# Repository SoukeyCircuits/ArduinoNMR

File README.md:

August 2026 Update and Explainer:

IMPORTANT DISCLAIMER: The repository here is only the spectrometer for an NMR. You will need to purchase a sufficiently homogeneous magnet and a power amplifier to acquire any kind of measurement. A power amplifier can be purchased from aliexpress for under $100 but your quality and safety will vary significantly. If you are looking for a magnet, there are a few open source options that you can build yourself or commercially available ones.

The magnet used for demonstration can be found here: 
https://www.spincore.com/products/Magnets/
I will do a build of this one: 
https://www.hardware-x.com/article/S2468-0672(25)00029-X/fulltext 
I'm unsure if this is of high quality but would be an interesting build:
https://science.slc.edu/mfrey/project/3dprintnmrmandhalas_update2/

To do list: 
	
  -Upload Accessory PCB files
	
  -Add alternative attenuator and LNA (10 MHz minimum frequency but lower price).
	
  -Upload control code
	
  -Upload Arduino NMR pulse code (being edited for release)
	
  -Upload CAD/CAM designs for the housing and end plates
	
  -Add Arduino Giga Display + display software
	
  -Show preliminary results from working device
	
  -Add non JLC BOM (Mouser, Aliexpress, etc)
	
  -Add raspberry pi multiple instrument control software.

  -Fix phase error discovered at OpenSauce 2026.
  
  -Implement digital filtering techniques.
  
The main sections of the Arduino NMR are the RF synthesis, RF input, and the Tayloe detector. 

RF synthesis begins with the SI5351A-B-GM chip connected to an ABM8G-25.000MHZ-4Y-T3, a  25 MHz crystal oscillator. The 20QFN package for the SI5351 was specifically chosen over the 16QFN as it was having issues with the Etherkit SI5351 library and not indexing the clock outputs correctly. The SI5351A-B-GM is still unable to use CLK6 and CLK7 as they are handled differently from CLK0-CLK5. Although it would be possible to control all 8 outputs, the function is sufficient for the design as is. The primary output clocks CLK0-CLK3 are connected to an ADG904BRUZ in an SP4T configuration. The switch allows for indexing either 0°, 90°, 180°, and 270° phase for a single frequency or 0° and a second phase at two separate frequencies. The lowest frequency for a 0°-90° control is 4.76 MHz due to the lower PLL limit of 600 MHz and the upper divider limit of int-127. For 0°-90°-180°, the lower limit is twice that at 9.52 MHz. Finally, for full 0°-90°-180°-270° control, the lower limit is 14.17 MHz.

The output is then fed into a PE4251MLI-Z SPDT switch. Since both single and dual frequency setups have an available channel containing the 0° at the Larmor frequency, when not transmitting, the channel can be used for Homodyne demodulation. Alternatively, one of the clocks can be set to a secondary offset frequency for Heterodyne demodulation. 

When actively transmitting, the output is sent through a PE43650 attenuator for digital control of the RF power output. Although the PE43650 was chosen based on availability and price, it would be advantageous to include the PE43711B-Z as an option in the future. The PE43650 has 0.5 dB step sizes with a maximum attenuation of 15.5 dB, but an improvement with the PE43711B-Z would give 0.25 dB step sizes and a maximum attenuation of 31.5 dB. For these applications, 0.5 dB is sufficient and maximum power can be limited by an external attenuator on the output(s).

fter attenuation, the final stage is either a bridged solder jumper, or another PE4251MLI-Z SPDT switch. This switch is what controls the two TX output options. Each output will need its own external attenuator to limit the maximum power output as well as a filter. The SI5351 only emits a square shaped output and harmonic frequencies must be filtered out for a pure sinusoidal output at the desired frequency. This allows for connecting a single spectrometer to multiple instruments each with their own dedicated TX and RX ports.

After amplification, further accessory parts are available for filtering, conditioning, and pulse breakthrough limitation. All of these accessories fit inside a 50x25x25mm aluminum enclosure available on Aliexpress but require drilling holes for the SMA connectors. The first accessory is the LC filter. This design is able to fit a 7 pole LC filter within the small enclosure for high off frequency rejection for both ≤100W and ≤5W depending on which side is populated. 

Another accompanying accessory is the crossed-diode duplexer to reject low power noise from the amplifier while passing the high powered pulse. By populating the diodes at the top of the design and not populating the lower diodes, this gives a path of 3 pairs of crossed diodes before reaching the center SMA port leading to the magnet. By changing the diodes populated to the bottom half of the board, bridging the top solder jumper, and not including the center SMA header, the same board can be used for crossed diodes to ground. It should be said, never try to combine these two functions as they are for separate uses and it could damage your equipment.

When attempting to capture the NMR signal, always filter before the signal enters the RX ports. Like with the TX ports, the signal can either go into the default solder bridged SMA connector, or be actively switched between the two RX ports. Once the signal has entered the RX portion of the board, there is one additional PE4251MLI-Z SPDT switch to protect the preamplifier from the pulse breakthrough. This switch is normally closed to a 50 Ω terminator but can be GPIO controlled to open after the desired deadtime. When open, the signal passes into a multiple stage low noise amplifier (LNA). The LNA is a dual stage PHA-13HLN+ amplifier with approximately 48-51 dB of gain with a noise figure ≤3. An additional design with budget conscience in mind alternatively uses a dual GALI-S66+ design for $10 instead of $30. This design has a smaller 42 dB gain and has a similar noise figure above 10 MHz but the noise figure skyrockets below 10 MHz. 

After the preamplifier, the design has one of two options for configuration, bridging the triple solder pad to the left, sends the signal directly into the Tayloe detector. Alternatively, bridging the solder to the right and additionally at the end allows for additional filtering after the LNA. If RX1 and RX2 are close in frequency, the filter can be set to cut off just at the frequency of interest. If the desire is for wide band operation from 1-100 MHz, it is advised to still filter the 100+ MHz frequency as both LNAs have additional noise at or above that frequency. The performance of the LNA and accompanying filtering can be measured by disconnecting C43, not powering the 5V line, and connecting to the center SMA connector as the output. It is advised to validate the gain and noise figure of the LNA prior to connecting to the SN74LV4052ADR. 

Once the signal is amplified and filtered, the signal will pass through the C43 DC blocking capacitor and enter a DC offset of 1.66V using a 3.3V voltage splitter. The signal will then enter the SN74LV4052ADR setup in the configuration of a Tayloe detector inspired by the ESP32 designed https://github.com/thaaraak. As a brief overview, by mixing the 0° and 90° signals from the SI5351 into the SN74LV4052ADR A & B pins and our amplified signal into the COM port, we are able to split the IF into their 0°, 90°, 180°, and 270° components. By then connecting the 0° to the positive end and 180° into the negative end of an operational amplifier, the in-phase signal is the resulting output and can be measured. By repeating with the 90° and 270° components, the quadrature signal can also be acquired. 

Finally, the I/Q signal is measured using the Arduino Giga’s built in ADC pins. Since the clock frequency of the Arduino Giga is 480 MHz, the ADC is capable of measuring up to 12.5 Msps for each channel. This uses the https://github.com/Bexin3/STMSpeeduino as a starting point but uses my built in pulse control software to handle the timing. 

## Repository layout

See `CHANGELOG.md` for what changed since June.

- `BOM_09_23_26.csv` — every part for the main board: JLCPCB assembly, hand solder (front and back), and off-board items with links
- `Arduino_NMR_09_23_26/KiCad_Files/Arduino_NMR_5.4.kicad_pro` — main board; open in KiCad 10
- `Arduino_NMR_09_23_26/KiCad_Files/production/1_jlcpcb_assembly.csv` + `1_jlcpcb_assembly_cpl.csv` — the files to upload to JLCPCB
- `Arduino_NMR_09_23_26/Power-USBC/` — USB-C PD power board (9 V in, +8 V / +3.3 V out)
- `Arduino_NMR_09_23_26/Power_Barrel/` — barrel-jack version of the power board
- `Past Boards/` — earlier revisions, kept as they were

Each power board folder has its own README, BOM, schematic PDF and JLCPCB files. Released boards are tagged in git (e.g. `v5.4-production`).

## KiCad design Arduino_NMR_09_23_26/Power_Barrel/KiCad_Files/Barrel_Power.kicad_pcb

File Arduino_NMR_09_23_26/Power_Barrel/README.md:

# Power_Barrel

Barrel-jack version of the Power-USBC board. The PD negotiation and interlock are gone. It takes a DC input on J1 (PJ-058B), makes the +8 V (BD80GC0VEFJ-ME2) and +3.3 V (BD33GA5WEFJ-E2) rails, and feeds the main board over the same J2 (1×12) and J4 (2×5 right-angle) connectors.

| File | What |
|---|---|
| `BOM_Barrel_09_23_26.csv` | every part: JLCPCB assembly, hand solder, and off-board items |
| `Barrel_Power_schematic.pdf` | the schematic |
| `KiCad_Files/Barrel_Power.kicad_pro` | open this in KiCad 10 |
| `KiCad_Files/production/1_jlcpcb_assembly.csv` + `_cpl.csv` | the files to upload to JLCPCB |

## Status

**Not yet built or ordered.** The input voltage range hasn't been confirmed against the regulators; check the BD80 dropout before choosing a supply. IC25 is out of stock at JLC, so hand solder it.

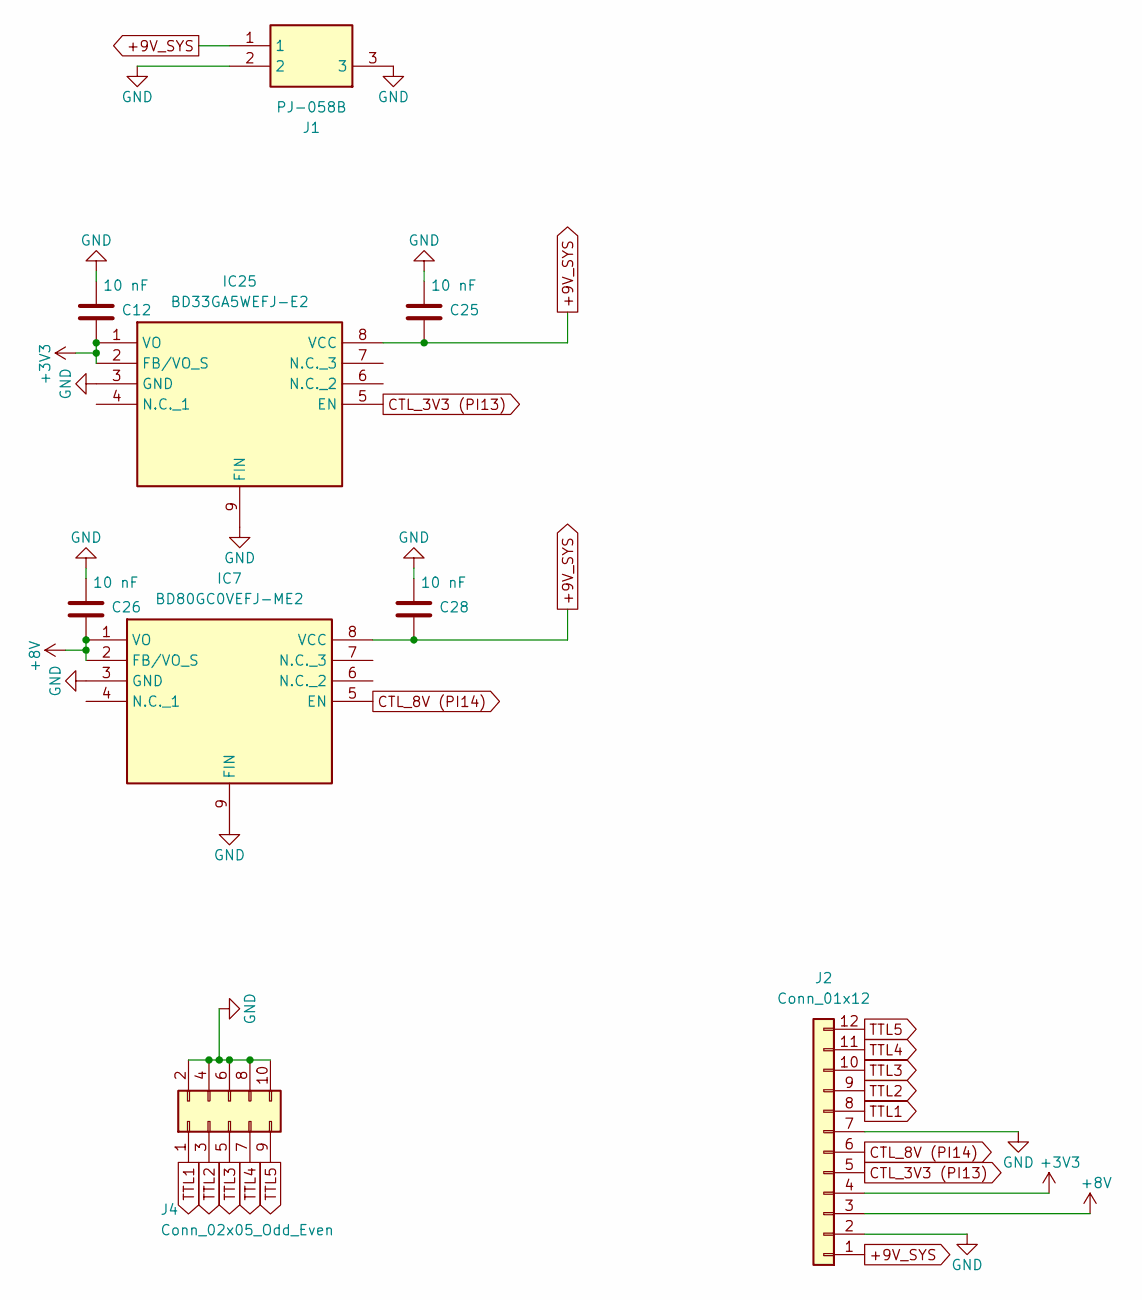
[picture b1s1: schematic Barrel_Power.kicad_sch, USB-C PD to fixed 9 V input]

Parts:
C12, C25, C26, C28: 10 nF; C_0805_2012Metric_Pad1.18x1.45mm_HandSolder
IC7: BD80GC0VEFJ-ME2; SOIC127P600X100-9N; Mouser Part Number 755-BD80GC0MEFJ-ME2
IC25: BD33GA5WEFJ-E2; SOIC127P600X100-9N; Mouser Part Number 755-BD80GC0MEFJ-ME2
J1: PJ-058B; PJ058B; Mouser Part Number 490-PJ-058B
J2: Conn_01x12; PinHeader_1x12_P2.54mm_Vertical
J4: Conn_02x05_Odd_Even; PinHeader_2x05_P2.54mm_Horizontal

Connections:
+3V3: C12.1, IC25.1 (VO), IC25.2 (FB/VO_S), J2.4
+8V: C26.1, IC7.1 (VO), IC7.2 (FB/VO_S), J2.3
+9V_SYS: C25.1, C28.1, IC7.8 (VCC), IC25.8 (VCC), J1.1, J2.1
CTL_3V3 (PI13): IC25.5 (EN), J2.5
CTL_8V (PI14): IC7.5 (EN), J2.6
GND: C12.2, C25.2, C26.2, C28.2, IC7.3 (GND), IC7.9 (FIN), IC25.3 (GND), IC25.9 (FIN), J1.2, J1.3, J2.2, J2.7, J4.2, J4.4, J4.6, J4.8, J4.10
TTL1: J2.8, J4.1
TTL2: J2.9, J4.3
TTL3: J2.10, J4.5
TTL4: J2.11, J4.7
TTL5: J2.12, J4.9

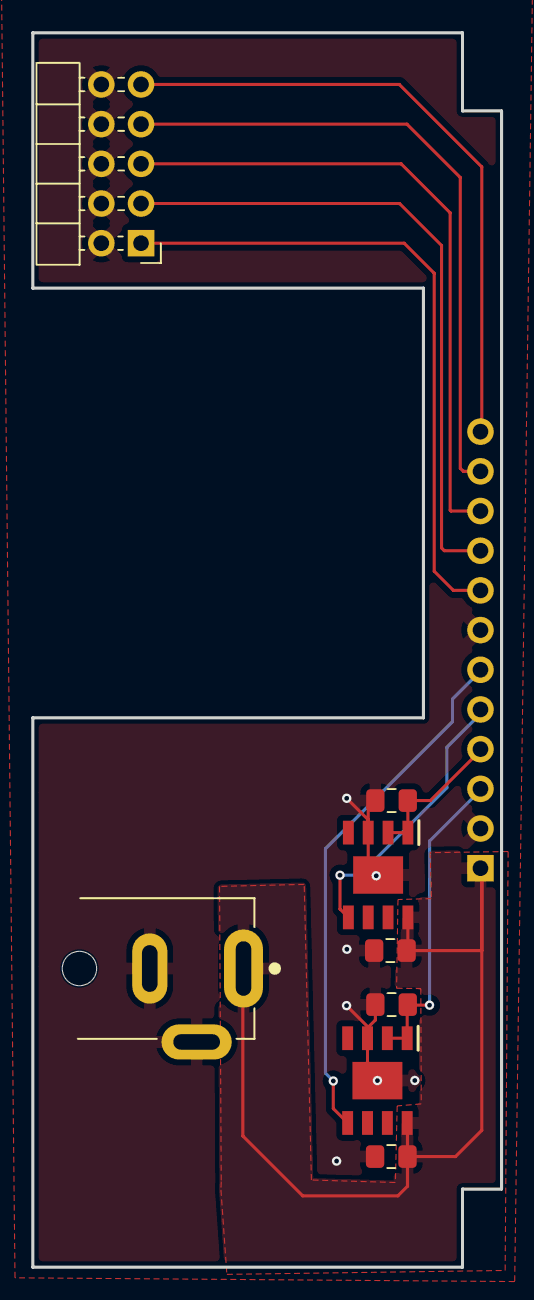
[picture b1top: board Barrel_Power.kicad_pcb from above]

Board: 2 copper layers, 30.0 x 79.0 mm, 9 parts (0 on the bottom side), 11 nets.

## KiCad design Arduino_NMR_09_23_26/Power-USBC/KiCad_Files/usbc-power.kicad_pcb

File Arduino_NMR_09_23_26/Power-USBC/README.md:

# Power-USBC

USB-C PD power board for the Arduino NMR. It negotiates a fixed 9 V from any USB-C PD supply (HUSB238A-BB001), makes the +8 V (LNA) and +3.3 V rails on board, and feeds them to the main board over J2 (1×12) and J4 (2×5 right-angle).

- **Over-voltage interlock:** a TL431A cuts the input if the supply ever delivers more than ~10 V.
- **Indicators:** LED1–LED3 show +9V_SYS, +8V and +3V3.
- **2 layers, 1.6 mm.**

| File | What |
|---|---|
| `BOM_USBC_09_23_26.csv` | every part: JLCPCB assembly, hand solder, and off-board items |
| `USBC_Power_schematic.pdf` | the schematic |
| `KiCad_Files/usbc-power.kicad_pro` | open this in KiCad 10 |
| `KiCad_Files/production/1_jlcpcb_assembly.csv` + `_cpl.csv` | the files to upload to JLCPCB |

## Known issues

- **The R23 failsafe is in the schematic but not on the PCB.** The schematic has R23 and R32 at 6.04k in parallel, so a single failed resistor gives 12 V (caught by the interlock) instead of 28 V. The PCB and BOM still have a single 3.00k R23. Run *Update PCB from Schematic* before the next order.
- **J10 (USB-C receptacle):** JLC doesn't stock the GCT USB4105-GF-A-120 (48 V). Either hand solder it or switch to the HRO TYPE-C-31-M-12 (C165948), which is rated 20 V only.
- **IC25 (BD33GA5WEFJ-E2)** is out of stock at JLC. Hand solder it.
- **D20 (SMAJ24A)** clamps at 38.9 V, which is above U20's 33 V absolute maximum. Acceptable for a test board.

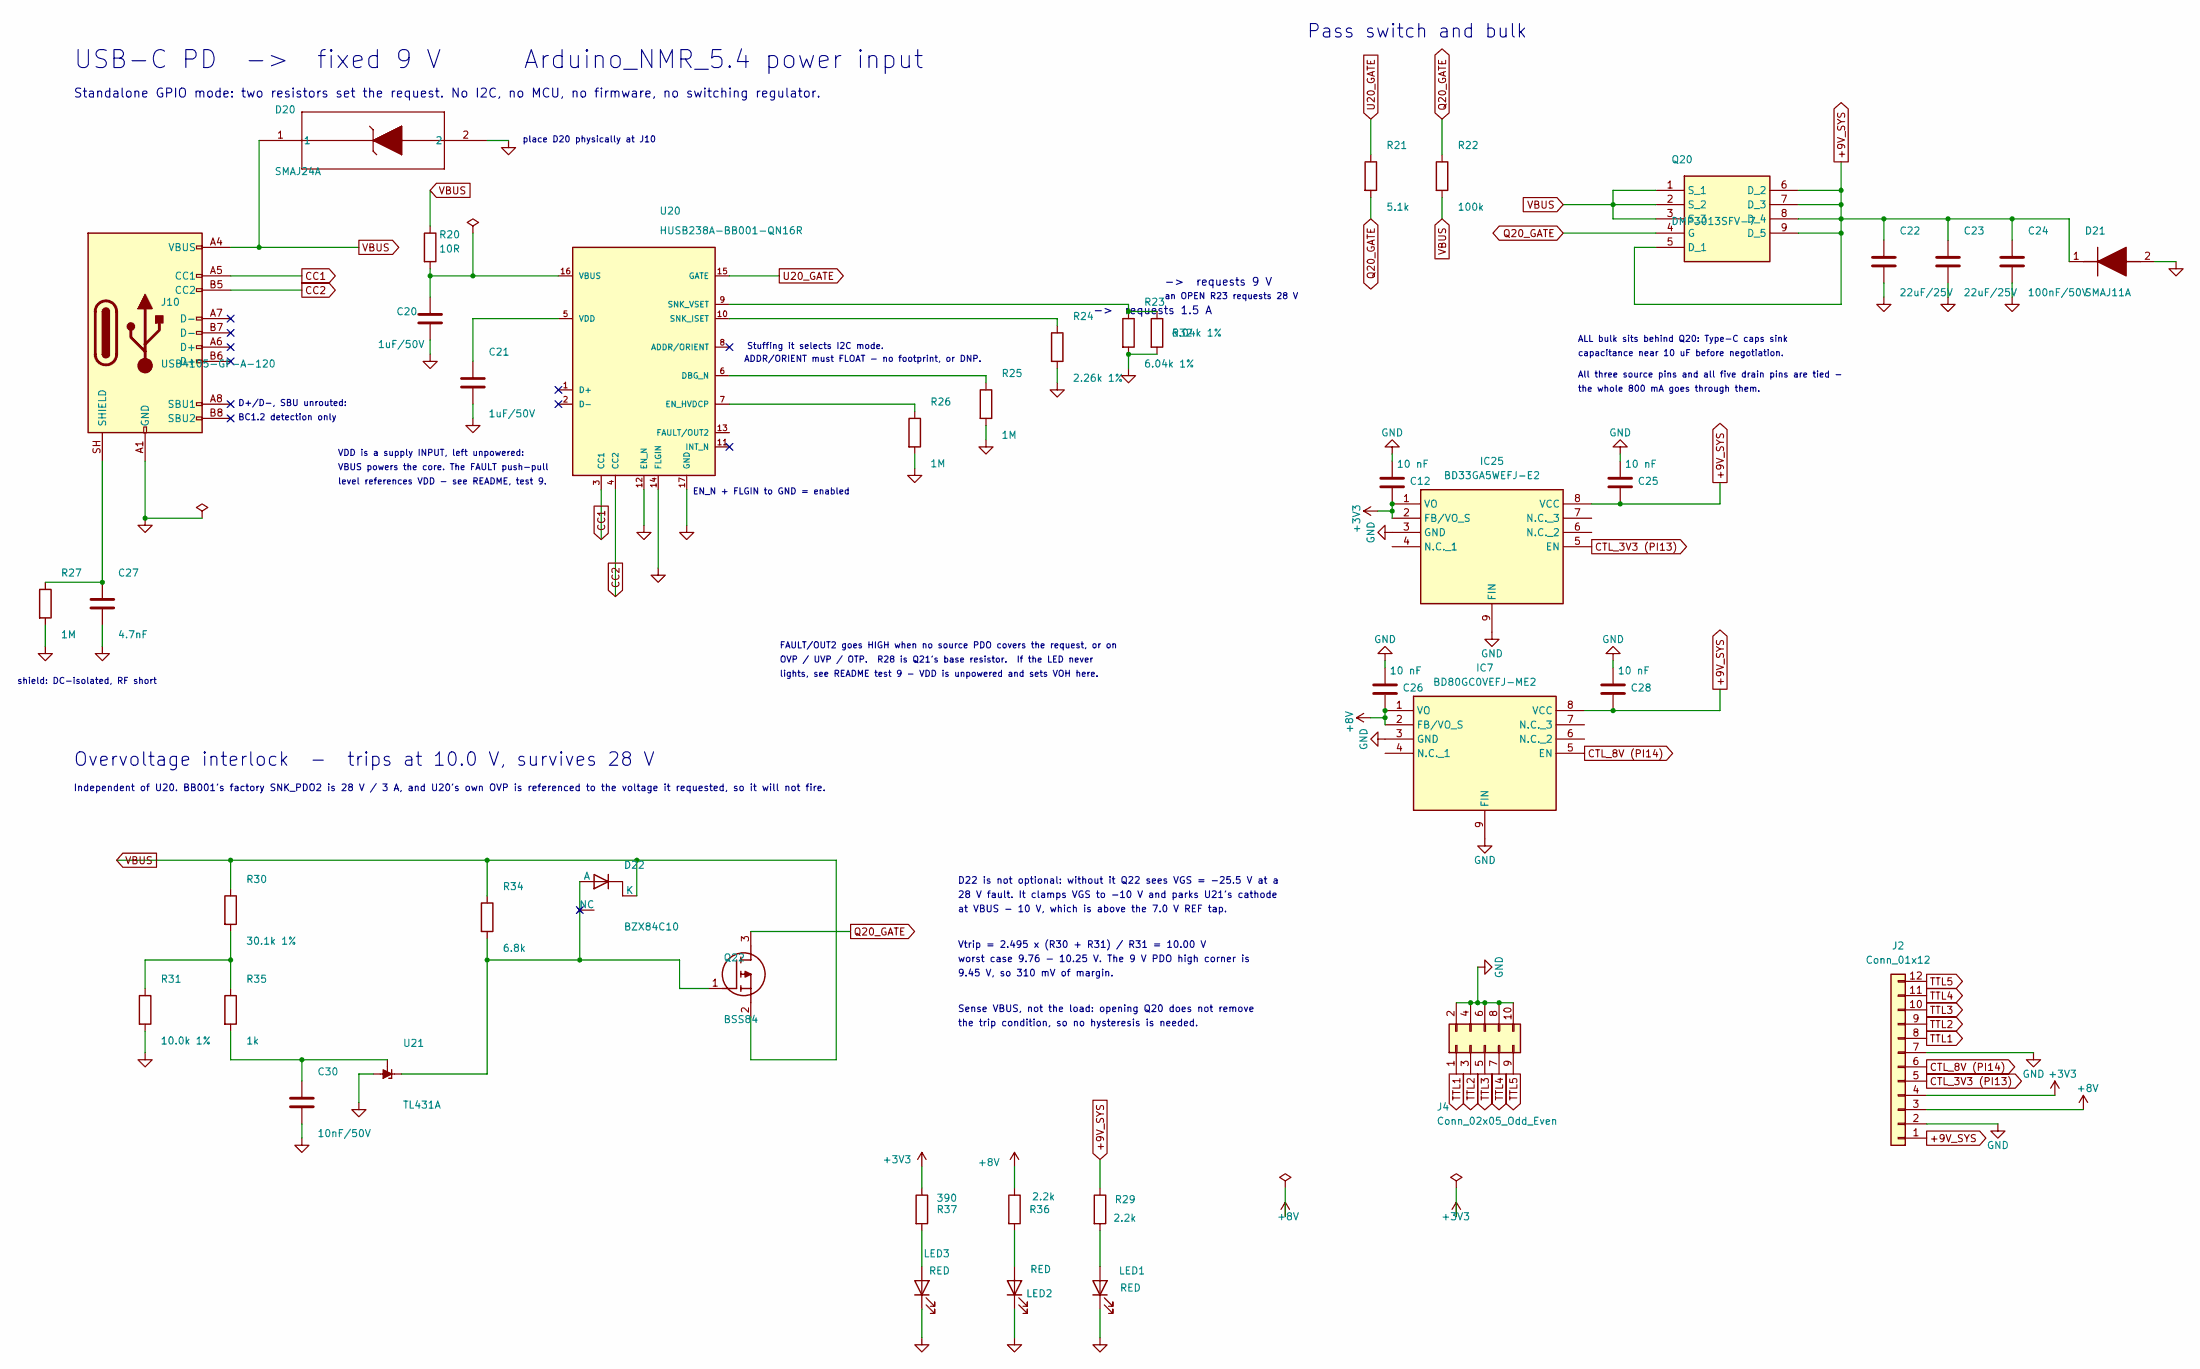
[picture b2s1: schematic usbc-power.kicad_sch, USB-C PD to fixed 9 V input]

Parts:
C12, C25, C26, C28: 10 nF; C_0805_2012Metric_Pad1.18x1.45mm_HandSolder
C20, C21: 1uF/50V; C_0603_1608Metric
C22, C23: 22uF/25V; C_1206_3216Metric
C24: 100nF/50V; C_0402_1005Metric
C27: 4.7nF; C_0402_1005Metric
C30: 10nF/50V; C_0402_1005Metric
D20: SMAJ24A; SMASeries_LTF; LCSC C132947
D21: SMAJ11A; DIOM5127X229N
D22: BZX84C10; P200_SOT-23; LCSC C118575
IC7: BD80GC0VEFJ-ME2; SOIC127P600X100-9N; Mouser Part Number 755-BD80GC0MEFJ-ME2
IC25: BD33GA5WEFJ-E2; SOIC127P600X100-9N; Mouser Part Number 755-BD80GC0MEFJ-ME2
J2: Conn_01x12; PinHeader_1x12_P2.54mm_Vertical
J4: Conn_02x05_Odd_Even; PinHeader_2x05_P2.54mm_Horizontal
J10: USB4105-GF-A-120; USB_C_Receptacle_GCT_USB4105-xx-A_16P_TopMnt_Horizontal
LED1, LED2, LED3: RED; LED_0805_2012Metric; LCSC C2295
Q20: DMP3013SFV-7; DMP3036SFV7; LCSC C264098
Q22: BSS84; SOT95P240X120-3N; LCSC C114481
R20: 10R; R_0402_1005Metric
R21: 5.1k; R_0402_1005Metric
R22: 100k; R_0402_1005Metric
R23, R32: 6.04k 1%; R_0402_1005Metric
R24: 2.26k 1%; R_0402_1005Metric
R25, R26, R27: 1M; R_0402_1005Metric
R29, R36: 2.2k; R_0402_1005Metric
R30: 30.1k 1%; R_0402_1005Metric
R31: 10.0k 1%; R_0402_1005Metric
R34: 6.8k; R_0402_1005Metric
R35: 1k; R_0402_1005Metric
R37: 390; R_0402_1005Metric
U20: HUSB238A-BB001-QN16R; QFN-16-1EP_3x3mm_P0.5mm_EP1.7x1.7mm_ThermalVias; LCSC C24833806
U21: TL431A; SOT-23

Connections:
+3V3: C12.1, IC25.1 (VO), IC25.2 (FB/VO_S), J2.4, R37.1
+3V3_USB: C21.1, U20.5 (VDD)
+8V: C26.1, IC7.1 (VO), IC7.2 (FB/VO_S), J2.3, R36.1
+9V_SYS: C22.1, C23.1, C24.1, C25.1, C28.1, D21.1 (K), IC7.8 (VCC), IC25.8 (VCC), J2.1, Q20.5 (D_1), Q20.6 (D_2), Q20.7 (D_3), Q20.8 (D_4), Q20.9 (D_5), R29.1
CC1: J10.A5 (CC1), U20.3 (CC1)
CC2: J10.B5 (CC2), U20.4 (CC2)
CTL_3V3 (PI13): IC25.5 (EN), J2.5
CTL_8V (PI14): IC7.5 (EN), J2.6
GND: C12.2, C20.2, C21.2, C22.2, C23.2, C24.2, C25.2, C26.2, C27.2, C28.2, C30.2, D20.2, D21.2 (A), IC7.3 (GND), IC7.9 (FIN), IC25.3 (GND), IC25.9 (FIN), J2.2, J2.7, J4.2, J4.4, J4.6, J4.8, J4.10, J10.A1 (GND), J10.A12 (GND), J10.B1 (GND), J10.B12 (GND), LED1.1 (K), LED2.1 (K), LED3.1 (K), R23.2, R24.2, R25.2, R26.2, R27.2, R31.2, R32.2, U20.12 (EN_N), U20.14 (FLGIN), U20.17 (GND), U21.3 (A)
unnamed: D22.1 (A), Q22.1 (G), R34.2, U21.1 (K)
unnamed: C27.1, J10.SH (SHIELD), R27.1
unnamed: LED1.2 (A), R29.2
unnamed: LED2.2 (A), R36.2
unnamed: LED3.2 (A), R37.2
unnamed: R30.2, R31.1, R35.1
unnamed: R25.1, U20.6 (DBG_N)
unnamed: R26.1, U20.7 (EN_HVDCP)
unnamed: R24.1, U20.10 (SNK_ISET)
unnamed: R23.1, R32.1, U20.9 (SNK_VSET)
unnamed: C20.1, R20.2, U20.16 (VBUS)
unnamed: C30.1, R35.2, U21.2 (REF)
Q20_GATE: Q20.4 (G), Q22.3 (D), R21.2, R22.1
TTL1: J2.8, J4.1
TTL2: J2.9, J4.3
TTL3: J2.10, J4.5
TTL4: J2.11, J4.7
TTL5: J2.12, J4.9
U20_GATE: R21.1, U20.15 (GATE)
VBUS: D20.1, D22.3 (K), J10.A4 (VBUS), J10.A9 (VBUS), J10.B4 (VBUS), J10.B9 (VBUS), Q20.1 (S_1), Q20.2 (S_2), Q20.3 (S_3), Q22.2 (S), R20.1, R22.2, R30.1, R34.1

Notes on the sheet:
VDD is a supply INPUT, left unpowered:
at VBUS - 10 V, which is above the 7.0 V REF tap.
lights, see README test 9 - VDD is unpowered and sets VOH here.
FAULT/OUT2 goes HIGH when no source PDO covers the request, or on
worst case 9.76 - 10.25 V. The 9 V PDO high corner is
an OPEN R23 requests 28 V
-> requests 9 V
capacitance near 10 uF before negotiation.
BC1.2 detection only
Pass switch and bulk
ALL bulk sits behind Q20: Type-C caps sink
place D20 physically at J10
D22 is not optional: without it Q22 sees VGS = -25.5 V at a
OVP / UVP / OTP. R28 is Q21's base resistor. If the LED never
-> requests 1.5 A
Independent of U20. BB001's factory SNK_PDO2 is 28 V / 3 A, and U20's own OVP is referenced to the voltage it requested, so it will not fire.
VBUS powers the core. The FAULT push-pull
Standalone GPIO mode: two resistors set the request. No I2C, no MCU, no firmware, no switching regulator.
Overvoltage interlock - trips at 10.0 V, survives 28 V
9.45 V, so 310 mV of margin.
shield: DC-isolated, RF short
the trip condition, so no hysteresis is needed.
level references VDD - see README, test 9.
Sense VBUS, not the load: opening Q20 does not remove
28 V fault. It clamps VGS to -10 V and parks U21's cathode
USB-C PD -> fixed 9 V Arduino_NMR_5.4 power input
the whole 800 mA goes through them.
Vtrip = 2.495 x (R30 + R31) / R31 = 10.00 V
EN_N + FLGIN to GND = enabled
Stuffing it selects I2C mode.
All three source pins and all five drain pins are tied -
ADDR/ORIENT must FLOAT - no footprint, or DNP.
D+/D-, SBU unrouted:

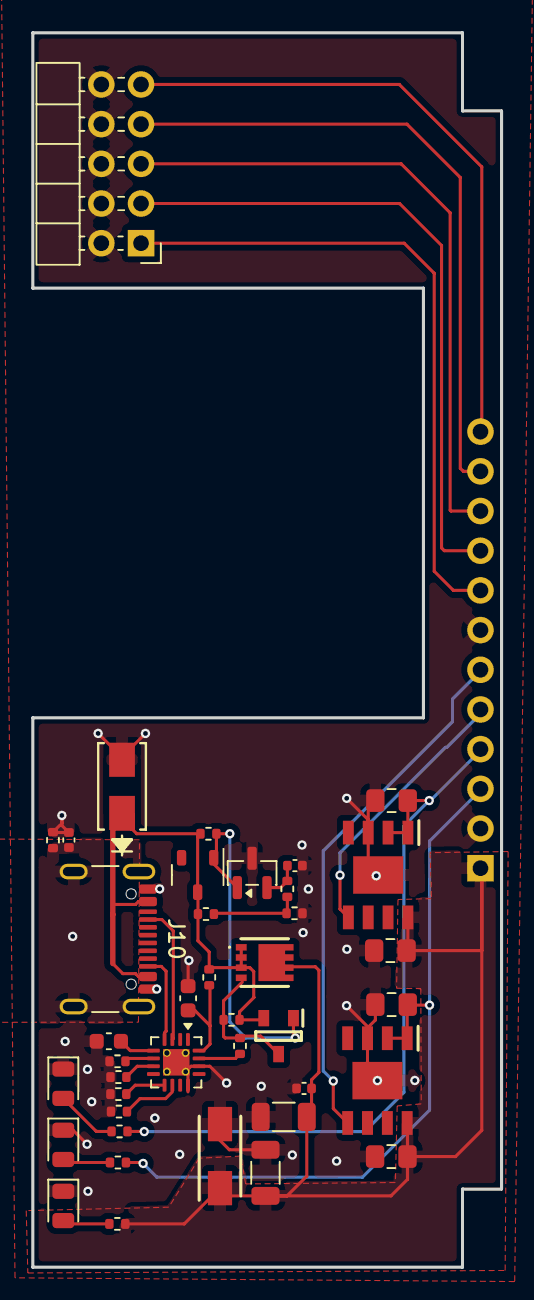
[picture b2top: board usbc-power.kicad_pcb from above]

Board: 2 copper layers, 30.0 x 79.0 mm, 41 parts (0 on the bottom side), 29 nets.

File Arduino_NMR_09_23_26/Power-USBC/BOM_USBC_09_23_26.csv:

Assembly,Value,Designator,Footprint,Qty,Category,Part Number,Supplier,Link,Notes
JLCPCB assembly (front),10 nF,"C12, C25, C26, C28",0805,4,SMD,,JLCPCB,,Pick from JLC suggested parts
JLCPCB assembly (front),1uF/50V,"C20, C21",0603,2,SMD,,JLCPCB,,Pick from JLC suggested parts
JLCPCB assembly (front),22uF/25V,"C22, C23",1206,2,SMD,,JLCPCB,,Pick from JLC suggested parts
JLCPCB assembly (front),100nF/50V,C24,0402,1,SMD,,JLCPCB,,Pick from JLC suggested parts
JLCPCB assembly (front),4.7nF,C27,0402,1,SMD,,JLCPCB,,Pick from JLC suggested parts
JLCPCB assembly (front),10nF/50V,C30,0402,1,SMD,,JLCPCB,,Pick from JLC suggested parts
JLCPCB assembly (front),SMAJ24A,D20,SMASeries_LTF,1,SMD,C132947,JLCPCB,,
JLCPCB assembly (front),SMAJ11A,D21,DIOM5127X229N,1,SMD,,JLCPCB,,Pick from JLC suggested parts
JLCPCB assembly (front),BZX84C10,D22,P200_SOT-23,1,SMD,C118575,JLCPCB,,
JLCPCB assembly (front),BD80GC0VEFJ-ME2,IC7,SOIC127P600X100-9N,1,SMD,,JLCPCB,,Pick from JLC suggested parts
JLCPCB assembly (front),USB4105-GF-A-120,J10,USB_C_Receptacle_GCT_USB4105-xx-A_16P_TopMnt_Horizontal,1,SMD,,JLCPCB,,"DECISION PENDING: GCT USB4105-GF-A-120 (48 V, 1.20 mm stakes for a 1.6 mm board) is not stocked by JLC - hand solder it, or switch the board to HRO TYPE-C-31-M-12 (C165948) which JLC stocks but is rated 20 V only."
JLCPCB assembly (front),RED,"LED1, LED2, LED3",0805,3,SMD,C2295,JLCPCB,,
JLCPCB assembly (front),DMP3013SFV-7,Q20,DMP3036SFV7,1,SMD,C264098,JLCPCB,,
JLCPCB assembly (front),BSS84,Q22,SOT95P240X120-3N,1,SMD,C114481,JLCPCB,,
JLCPCB assembly (front),10R,R20,0402,1,SMD,,JLCPCB,,Pick from JLC suggested parts
JLCPCB assembly (front),5.1k,R21,0402,1,SMD,,JLCPCB,,Pick from JLC suggested parts
JLCPCB assembly (front),100k,R22,0402,1,SMD,,JLCPCB,,Pick from JLC suggested parts
JLCPCB assembly (front),3.00k 1%,R23,0402,1,SMD,,JLCPCB,,Pick from JLC suggested parts
JLCPCB assembly (front),2.26k 1%,R24,0402,1,SMD,,JLCPCB,,Pick from JLC suggested parts
JLCPCB assembly (front),1M,"R25, R26, R27",0402,3,SMD,,JLCPCB,,Pick from JLC suggested parts
JLCPCB assembly (front),2.2k,"R29, R36",0402,2,SMD,,JLCPCB,,Pick from JLC suggested parts
JLCPCB assembly (front),30.1k 1%,R30,0402,1,SMD,,JLCPCB,,Pick from JLC suggested parts
JLCPCB assembly (front),10.0k 1%,R31,0402,1,SMD,,JLCPCB,,Pick from JLC suggested parts
JLCPCB assembly (front),6.8k,R34,0402,1,SMD,,JLCPCB,,Pick from JLC suggested parts
JLCPCB assembly (front),1k,R35,0402,1,SMD,,JLCPCB,,Pick from JLC suggested parts
JLCPCB assembly (front),390,R37,0402,1,SMD,,JLCPCB,,Pick from JLC suggested parts
JLCPCB assembly (front),HUSB238A-BB001-QN16R,U20,QFN-16-1EP_3x3mm_P0.5mm_EP1.7x1.7mm_ThermalVias,1,SMD,C24833806,JLCPCB,,
JLCPCB assembly (front),TL431A,U21,SOT-23,1,SMD,,JLCPCB,,Pick from JLC suggested parts
Hand solder (front),BD33GA5WEFJ-E2,IC25,SOIC127P600X100-9N,1,"ROHM BD33GA5WEFJ-E2 - 3.3 V LDO, HTSOP-J8",,,,OUT OF STOCK at JLCPCB (2 shortfall) - excluded from machine assembly. Hand solder after the board returns. Order separately.
Hand solder (front),Conn_01x12,J2,PinHeader_1x12_P2.54mm_Vertical,1,"2.54 mm pin header, 1x12 vertical",,AliExpress,https://www.aliexpress.us/item/3256806907643797.html,Cut to length from a 40P single-row 2.54 mm strip.
Hand solder (front),Conn_02x05_Odd_Even,J4,PinHeader_2x05_P2.54mm_Horizontal,1,"2.54 mm pin header, 2x5 right-angle",,AliExpress,https://www.aliexpress.us/item/3256806736246215.html,Right-angle dual-row header - mates coplanar with the RF board.
External (not on PCB),USB-C cable,,,1,"100 W, 1 m",,Amazon,https://www.amazon.com/dp/B0CJY9PRNY,
External (not on PCB),USB-C power supply,,,1,,,Amazon,https://www.amazon.com/dp/B0CYZHY7BX,
External (not on PCB),2.54 mm header sockets,,,1,Mating half for J2 / J4 on the RF board,,,,
External (not on PCB),M3 standoffs,,,1,Register the two boards so the connectors cannot slide a column,,AliExpress,https://www.aliexpress.us/item/3256808109877301.html,

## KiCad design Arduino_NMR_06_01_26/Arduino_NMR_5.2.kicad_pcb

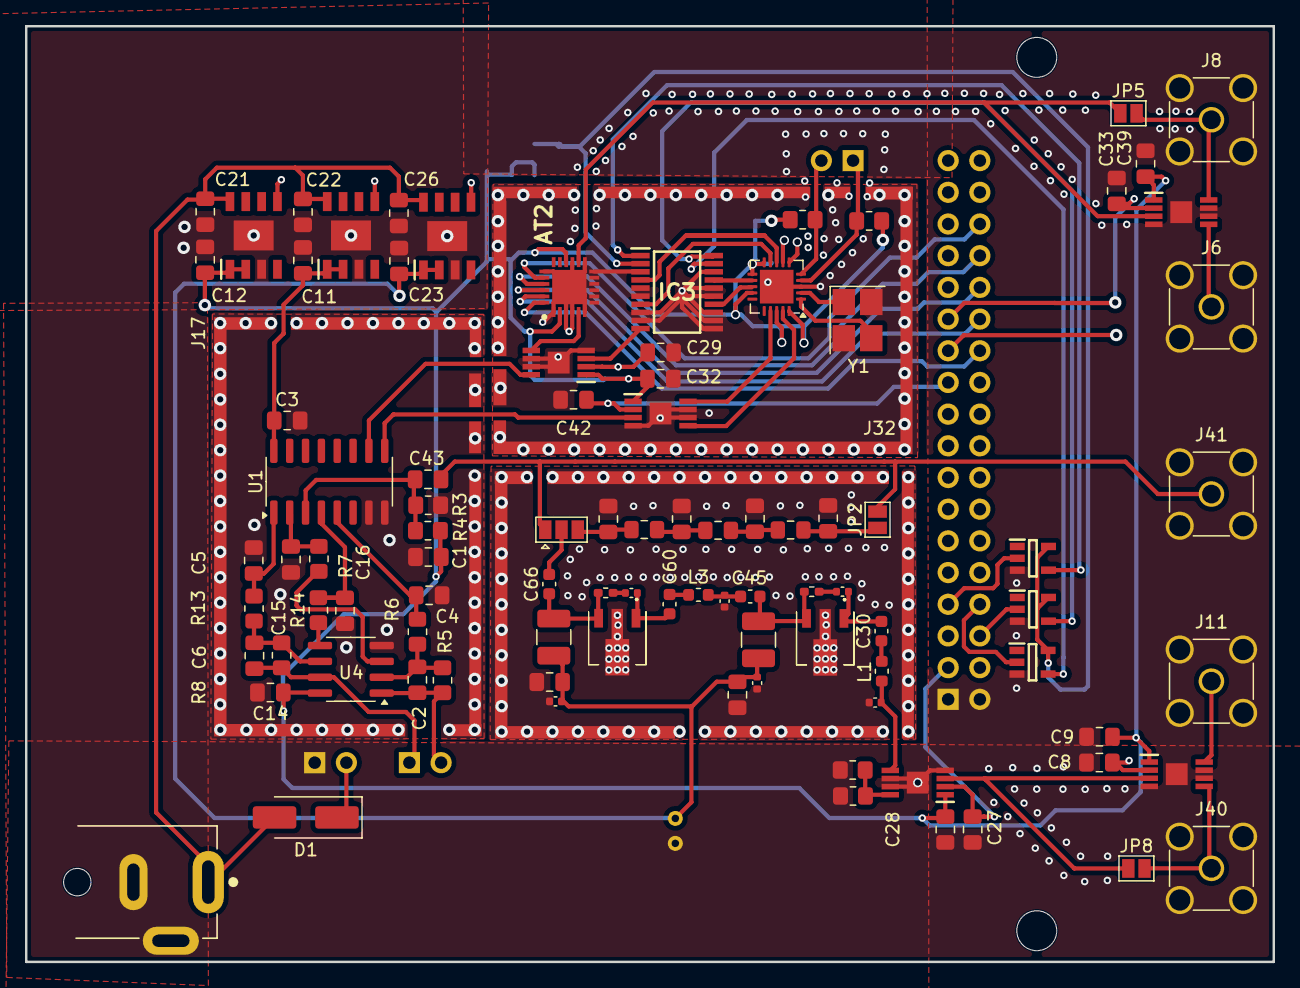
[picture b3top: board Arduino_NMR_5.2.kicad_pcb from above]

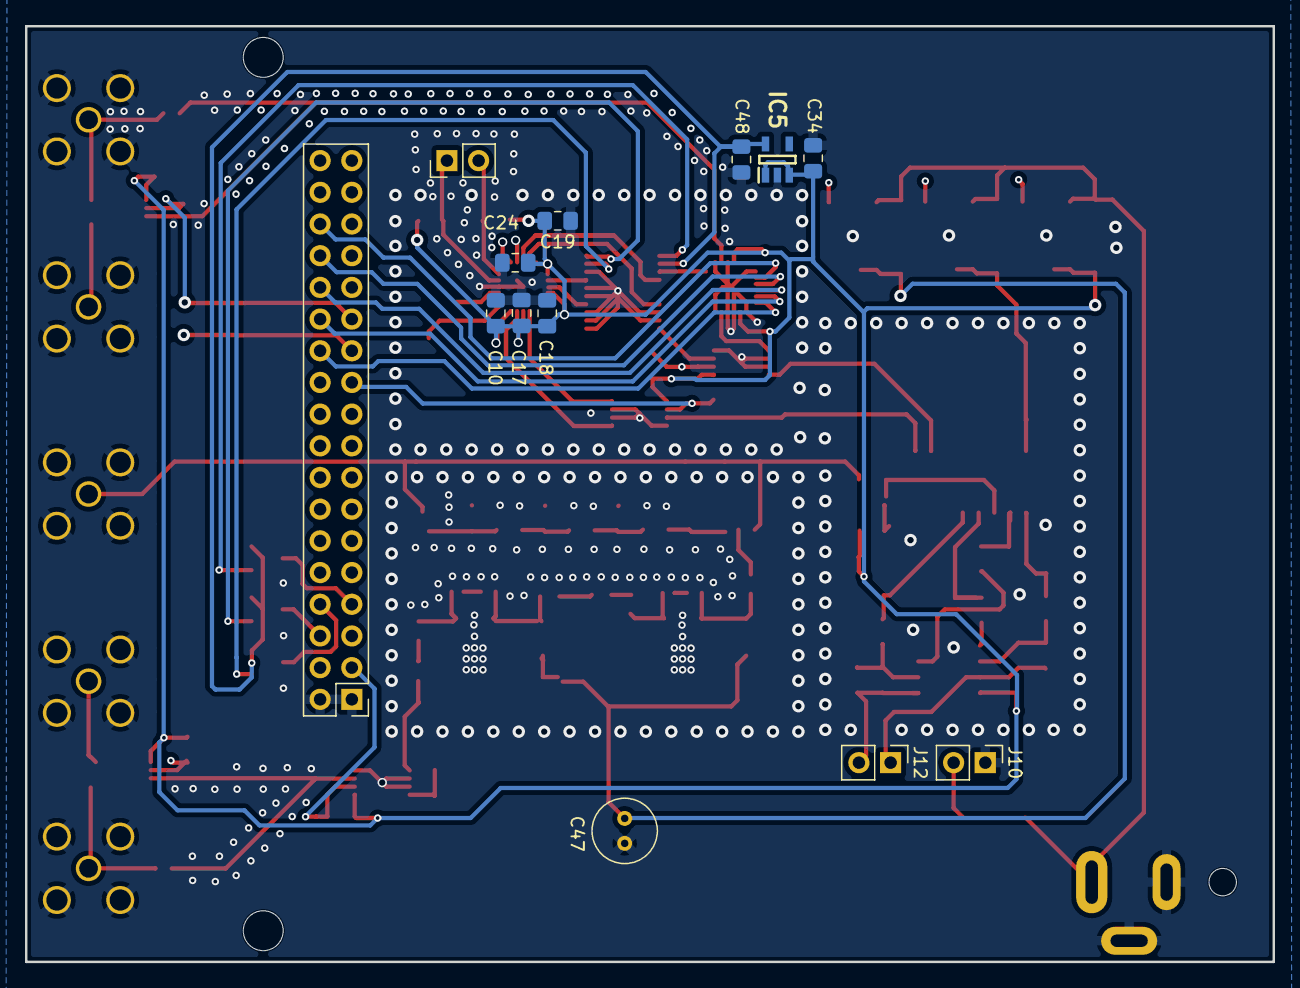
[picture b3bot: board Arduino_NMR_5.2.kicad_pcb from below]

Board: 4 copper layers, 100.0 x 75.0 mm, 108 parts (13 on the bottom side), 76 nets.

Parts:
AT2: PE43711B-Z
C1, C3, C10, C14, C17, C18, C19, C24, C34: 100 nF; C_0805_2012Metric_Pad1.18x1.45mm_HandSolder
C2, C4, C5, C6, C15, C16: 1 nF; C_0805_2012Metric_Pad1.18x1.45mm_HandSolder
C8, C9, C27, C28, C29, C32, C33, C39, C42: 100 pF; C_0805_2012Metric_Pad1.18x1.45mm_HandSolder
C11, C12, C21, C22, C23, C26: 10 nF; C_0805_2012Metric_Pad1.18x1.45mm_HandSolder
C20, C46: 1.5 pF; C_0402_1005Metric
C30, C45, C60, C66: 2.2 uF; C_0603_1608Metric
C31, C61: 100 nF; C_0402_1005Metric
C40, C64: 1 nF; C_0402_1005Metric
C41, C65: 10 uF; C_0805_2012Metric_Pad1.18x1.45mm_HandSolder
C43: 1 pF; C_0805_2012Metric_Pad1.18x1.45mm_HandSolder
C47: 100 uF; C_Radial_D5.0mm_H5.0mm_P2.00mm
C48: 1 uF; C_0805_2012Metric_Pad1.18x1.45mm_HandSolder
C62, C147: 47 pF; C_0805_2012Metric_Pad1.18x1.45mm_HandSolder
C141, C144: 180 pF; C_0805_2012Metric_Pad1.18x1.45mm_HandSolder
D1: D; D_SMA_Handsoldering
IC1, IC2, IC12: SN74LV1T04DBVR; SOT95P280X145-5N
IC3: ADG904BRUZ-REEL7; ADG904BRUZ
IC4, IC8, IC9, IC10, IC11: PE4251MLI-Z; SOP65P490X106-9N
IC5: TLV74125PDBVR; SOT95P280X145-5N
IC6: BD50GC0VEFJ-ME2; SOIC127P600X100-9N
IC7: BD80GC0VEFJ-ME2; SOIC127P600X100-9N
IC13, IC14: PHA-13HLN+; PHA13HLN
IC25: BD33GA5WEFJ-E2; SOIC127P600X100-9N
J1: PJ-058B; PJ058B
J4, J10, J12: Conn_01x02; PinHeader_1x02_P2.54mm_Vertical
J5: Digital; PinHeader_2x18_P2.54mm_Vertical
J6, J41: Ringdown; SMA_Amphenol_901-144_Vertical
J8: TX1; SMA_Amphenol_901-144_Vertical
J11: RX1; SMA_Amphenol_901-144_Vertical
J16: RFShield_OnePiece; RF Shield_1
J17: RFShield_OnePiece; RF Shield_3
J32: RFShield_OnePiece; RF Shield_2
J40: RX2; SMA_Amphenol_901-144_Vertical
JP2, JP5, JP8: Jumper_2_Open; SolderJumper-2_P1.3mm_Open_Pad1.0x1.5mm
JP4: SolderJumper_3_Open; SolderJumper-3_P1.3mm_Open_Pad1.0x1.5mm
L1, L3: 0603CS-5N1XJLW; L_0603_1608Metric
L2, L15: LQH32DZ150K53L; L_1210_3225Metric_Pad1.42x2.65mm_HandSolder
L13, L47: 330 nH; L_0805_2012Metric_Pad1.15x1.40mm_HandSolder
L44: 470 nH; L_0805_2012Metric_Pad1.15x1.40mm_HandSolder
R1, R6, R7, R13, R14, R15: 100Ω; R_0805_2012Metric_Pad1.20x1.40mm_HandSolder
R3, R4, R9, R10: 10kΩ; R_0805_2012Metric_Pad1.20x1.40mm_HandSolder
R5, R8: 1kΩ; R_0805_2012Metric_Pad1.20x1.40mm_HandSolder
R16, R17: 1.5 k; R_0402_1005Metric_Pad0.72x0.64mm_HandSolder
U1: SN74LV4052ADR; SOIC-16_3.9x9.9mm_P1.27mm
U2: Si5351A-B-GM; QFN-20-1EP_4x4mm_P0.5mm_EP2.7x2.7mm
U4: LM4562MAX/NOPB; SOIC-8-1EP_3.9x4.9mm_P1.27mm_EP2.29x3mm_nobottomgnd
Y1: ABM8G-25.000MHZ-B4Y-T; Crystal_SMD_SeikoEpson_FA238-4Pin_3.2x2.5mm_HandSoldering

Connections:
2Y0_0: C15.2, R13.2, U1.1 (2Y0_0)
2Y1_90: C4.2, R6.2, U1.5 (2Y1_90)
2Y2_270: C5.2, R7.2, U1.2 (2Y2_270)
2Y3_180: C16.2, R14.2, U1.4 (2Y3_180)
+2V5: C48.1, IC1.5 (VCC), IC2.5 (VCC), IC3.2 (VDD), IC5.5 (OUT), IC12.5 (VCC)
+3V3: AT2.2 (VDD), AT2.16 (LE), C1.2, C9.2, C10.2, C12.1, C14.1, C17.2, C18.2, C19.2, C24.2, C28.2, C32.2, C34.2, C39.2, IC4.1 (V2), IC5.1 (IN), IC5.3 (EN), IC8.1 (V2), IC9.1 (V2), IC10.1 (V2), IC11.1 (V2), IC25.1 (VO), IC25.2 (FB/VO_S), R4.2, R9.2, R10.2, U2.10 (VDDOB), U2.11 (VDDOA), U2.14 (VDDOD), U2.18 (VDDOC), U2.20 (VDD), U4.8 (V+)
+5V: C3.1, C11.1, IC6.1 (VO), IC6.2 (FB/VO_S), U1.16 (VCC)
+8V: C23.1, C40.1, C41.1, C47.1, C64.1, C65.1, IC7.1 (VO), IC7.2 (FB/VO_S), L2.1, L15.1
+12V: C21.1, C22.1, C26.1, D1.2 (A), IC6.8 (VCC), IC7.8 (VCC), IC25.8 (VCC), J1.1
/Arduino Giga Sheet/Vin: D1.1 (K), J10.2
Attem_Demod: IC3.10 (RFC), IC8.3 (RFC)
Atten: AT2.5 (RF1), IC8.5 (RF1)
CLK0_RF4: IC3.14 (RF4), U2.13 (CLK0)
CLK1_RF2: IC3.17 (RF2), U2.12 (CLK1)
CLK2_RF3: IC3.7 (RF3), U2.9 (CLK2)
CLK3_RF1: IC3.4 (RF1), U2.8 (CLK3)
CLK_4_QA: IC9.5 (RF1), U2.19 (CLK4)
CLK_5_QB: IC9.8 (RF2), U2.17 (CLK5)
CTL_1 (J3): AT2.23 (C1), J5.26
CTL_2 (J2): AT2.22 (C2), J5.28
CTL_3V3 (PI13): IC25.5 (EN), J5.12
CTL_4 (J1): AT2.21 (C4), J5.30
CTL_5V (PI10): IC6.5 (EN), J5.14
CTL_8 (J0): AT2.20 (C8), J5.32
CTL_8V (PI14): IC7.5 (EN), J5.18
CTL_.5 (J4): AT2.24 (C0.5), J5.24
CTL_Demod1 (PK5): C42.2, IC9.2 (V1), J5.21
CTL_Demod2 (PK7): C29.2, IC8.2 (V1), J5.16
CTL_LPFA: IC2.4 (Y), IC3.20 (A0)
CTL_LPFA_HIGH (PE5): IC2.2 (A), J5.6
CTL_LPFB: IC1.4 (Y), IC3.19 (A1)
CTL_LPFB_HIGH (PE4): IC1.2 (A), J5.8
CTL_Pulse: IC3.1 (~EN), IC12.4 (Y)
CTL_Pulse_HIGH (PK0): IC12.2 (A), J5.7
CTL_RFIN (PK2): C27.2, IC4.2 (V1), J5.3
CTL_RX (PK4): C8.2, IC10.2 (V1), J5.23
CTL_TX (PK3): C33.2, IC11.2 (V1), J5.25
Demod_A: IC8.8 (RF2), U1.10 (A_0)
Demod_B: IC9.3 (RFC), U1.9 (B_90)
GND: AT2.1 (C0.25), AT2.3 (~P/S), AT2.4 (GND_1), AT2.6 (GND_2), AT2.7 (GND_3), AT2.8 (GND_4), AT2.9 (GND_5), AT2.10 (GND_6), AT2.11 (GND_7), AT2.12 (GND_8), AT2.13 (GND_9), AT2.15 (GND_10), AT2.19 (C16), AT2.25 (EP), C1.1, C3.2, C4.1, C5.1, C8.1, C9.1, C10.1, C11.2, C12.2, C14.2, C15.1, C16.1, C17.1, C18.1, C19.1, C20.1, C21.2, C22.2, C23.2, C24.1, C26.2, C27.1, C28.1, C29.1, C32.1, C33.1, C34.1, C39.1, C40.2, C41.2, C42.1, C46.1, C47.2, C48.2, C62.1, C64.2, C65.2, C141.1, C144.1, C147.1, IC1.3 (GND), IC2.3 (GND), IC3.3 (GND_1), IC3.5 (GND_2), IC3.6 (GND_3), IC3.8 (GND_4), IC3.9 (GND_5), IC3.11 (GND_6), IC3.12 (GND_7), IC3.13 (GND_8), IC3.15 (GND_9), IC3.16 (GND_10), IC3.18 (GND_11), IC4.4 (N/C_OR_GND), IC4.6 (GND_1), IC4.7 (GND_2), IC4.9 (EP), IC5.2 (GND), IC6.3 (GND), IC6.9 (FIN), IC7.3 (GND), IC7.9 (FIN), IC8.4 (N/C_OR_GND), IC8.6 (GND_1), IC8.7 (GND_2), IC8.9 (EP), IC9.4 (N/C_OR_GND), IC9.6 (GND_1), IC9.7 (GND_2), IC9.9 (EP), IC10.4 (N/C_OR_GND), IC10.6 (GND_1), IC10.7 (GND_2), IC10.9 (EP), IC11.4 (N/C_OR_GND), IC11.6 (GND_1), IC11.7 (GND_2), IC11.9 (EP), IC12.3 (GND), IC13.2 (GROUND), IC13.4 (GND), IC14.2 (GROUND), IC14.4 (GND), IC25.3 (GND), IC25.9 (FIN), J1.2, J1.3, J5.1, J5.2, J6.2 (Ext), J8.2 (Ext), J10.1, J11.2 (Ext), J16.1 (Shield_1), J17.1 (Shield_1), J32.1 (Shield_1), J40.2 (Ext), J41.2 (Ext), R1.2, R3.1, R15.2, U1.7 (GND), U1.8 (GND), U2.3 (A0), U2.21 (GND), U4.4 (V-), Y1.2, Y1.4
I_Signal: C2.1, J12.2, R5.1, U4.1
unnamed: C30.1, L1.1
unnamed: C31.2, R16.1
unnamed: C45.2, C46.2, L3.2
unnamed: C60.1, L3.1
unnamed: C61.2, R17.1
unnamed: C141.2, L13.1, L44.2
unnamed: C144.2, L44.1, L47.2
unnamed: IC4.8 (RF2), R1.1, R15.1
unnamed: C30.2, C31.1, IC13.1 (RF-IN)
unnamed: C45.1, IC13.3 (_RF-OUT_&_DC-IN), L2.2, R16.2
unnamed: C60.2, C61.1, IC14.1 (RF-IN)
unnamed: C66.1, IC14.3 (_RF-OUT_&_DC-IN), L15.2, R17.2
unnamed: C147.2, JP2.1 (A), L47.1
unnamed: C62.2, JP4.3 (B), L13.2
unnamed: C43.2, R3.2, R4.1, U1.3 (2-COM)
unnamed: U2.1 (XA), Y1.3
unnamed: U2.2 (XB), Y1.1
unnamed: R7.1, U4.3 (+)
unnamed: C2.2, R5.2, R6.1, U4.2 (-)
unnamed: R14.1, U4.5 (+)
unnamed: C6.2, R8.2, R13.1, U4.6 (-)
OEB_CTL (PK6): J5.19, U2.7 (OEB)
Preamp_out: C66.2, JP4.2 (C)
Q_Signal: C6.1, J12.1, R8.1, U4.7
RF_in_amp: C20.2, IC4.5 (RF1), L1.2
RF_in_filter_out: C43.1, J41.1 (In), JP2.2 (B), JP4.1 (A)
RX_A: IC10.8 (RF2), J11.1 (In)
RX_B: IC10.5 (RF1), J40.1 (In), JP8.2 (B)
RX_in: IC4.3 (RFC), IC10.3 (RFC), JP8.1 (A)
SCL: J4.1, R9.1, U2.4 (SCL)
SDA: J4.2, R10.1, U2.5 (SDA)
SSEN_CTL (PI15): J5.13, U2.6 (SSEN)
TX_A: IC11.8 (RF2), J8.1 (In), JP5.2 (B)
TX_B: IC11.5 (RF1), J6.1 (In)
TX_SWITCH: AT2.14 (RF2), IC11.3 (RFC), JP5.1 (A)

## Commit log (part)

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2025-07-24 README.md
2026-05-31 Add files via upload
    Committed is my most up to date PCB for the Arduino NMR project.
2026-06-01 Update README with June 2026 details and to-do list
    Added June 2026 update with to-do list and detailed explanations of the Arduino NMR system components and configurations.
